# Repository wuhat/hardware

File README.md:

# WUHAT

A HAT for the Raspberry PI inspired by the
[franzboard](https://github.com/franzboard) and compatible in terms of switch
and LED connections.

## Features

* 1 DS18B20 temperature sensor
* 3 tactile switches
* 4 LEDs
* 1 ADC with 2 channels accessible via a header
* 6 GPIO pins on a header, surrounded by GND, 5V, and 3.3V
* 1 I2C pin header (GND SDA SCL 3V3)

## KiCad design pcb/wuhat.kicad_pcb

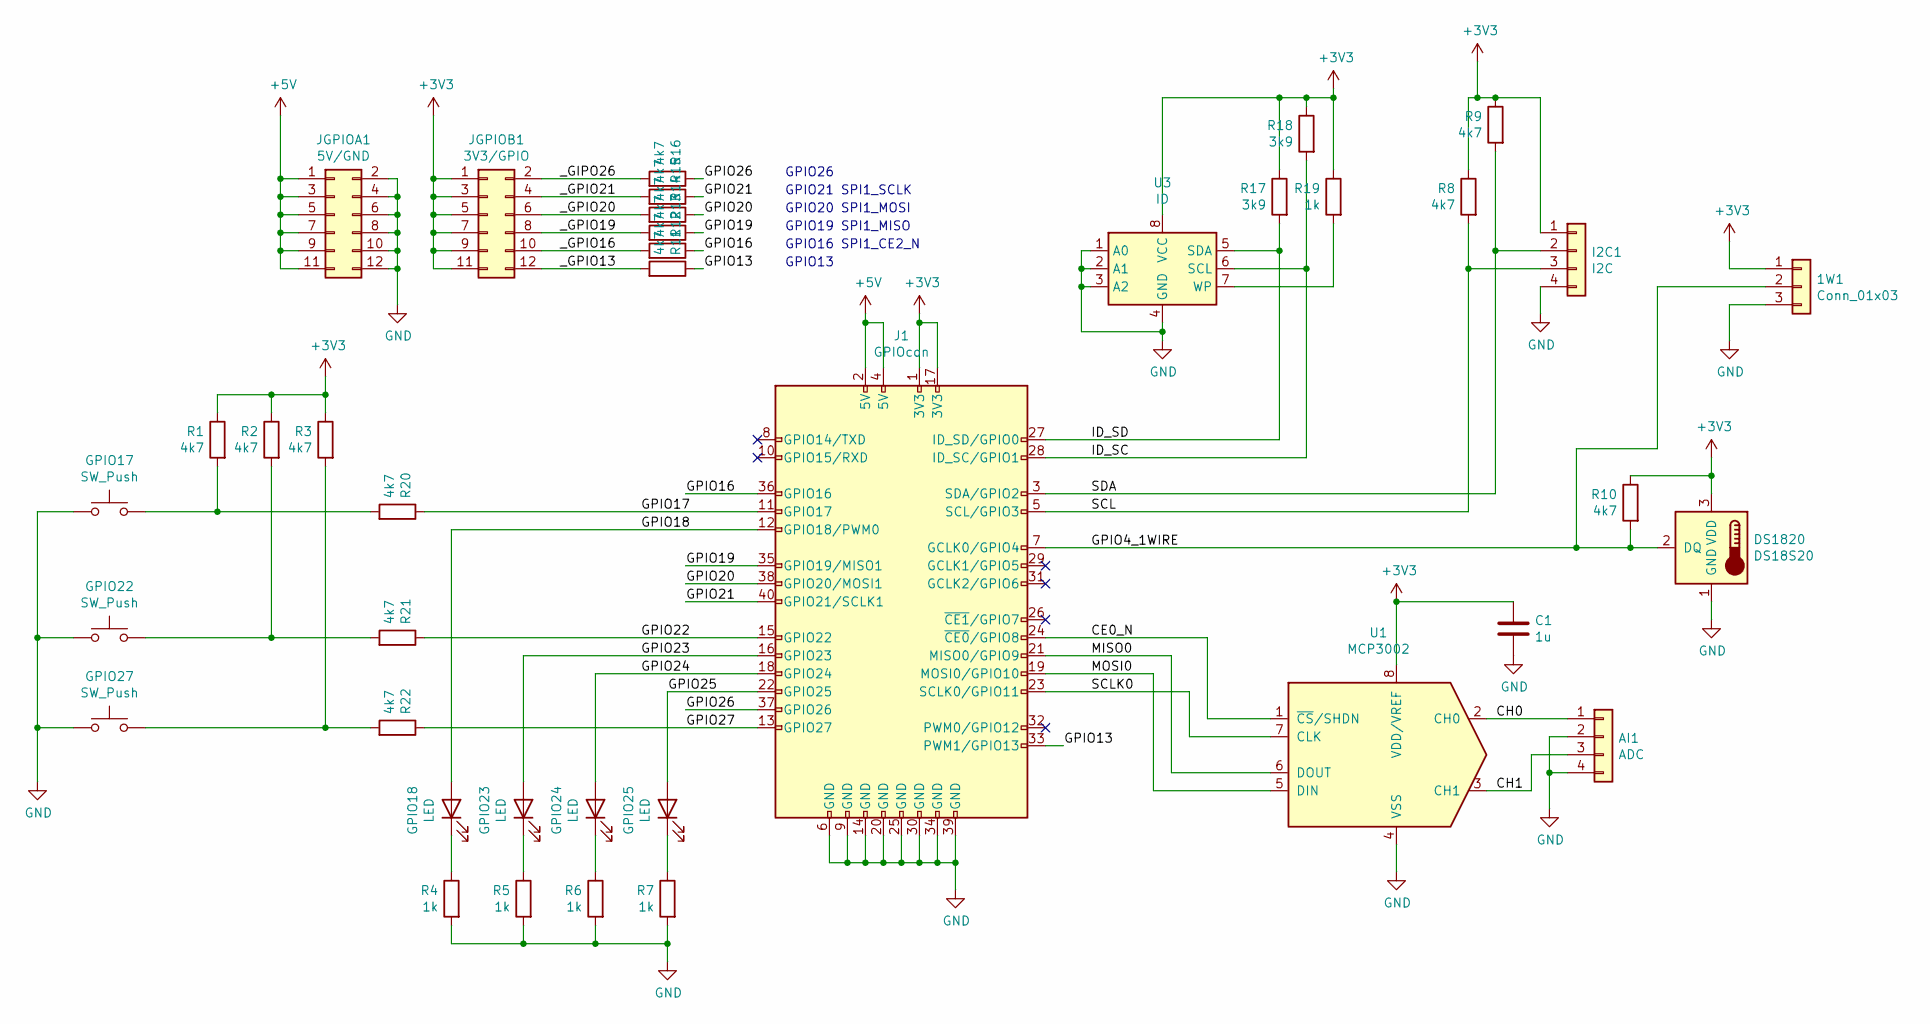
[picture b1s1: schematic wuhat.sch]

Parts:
1W1: Conn_01x03; PinHeader_1x03_P2.54mm_Vertical
AI1: ADC; PinHeader_1x04_P2.54mm_Vertical
C1: 1u; C_0603_1608Metric_Pad1.05x0.95mm_HandSolder
DS1820: DS18S20; TO-92_Inline_Wide
GPIO17, GPIO22, GPIO27: SW_Push; SW_PUSH_6mm
GPIO18, GPIO23, GPIO24, GPIO25: LED; LED_0603_1608Metric_Pad1.05x0.95mm_HandSolder
I2C1: I2C; PinHeader_1x04_P2.54mm_Vertical
J1: GPIOcon; PinHeader_2x20_P2.54mm_Vertical
JGPIOA1: 5V/GND; PinHeader_2x06_P2.54mm_Vertical
JGPIOB1: 3V3/GPIO; PinHeader_2x06_P2.54mm_Vertical
R1, R2, R3, R8, R9, R10, R11, R12, R13, R14, R15, R16, R20, R21, R22: 4k7; R_0603_1608Metric_Pad1.05x0.95mm_HandSolder
R4, R5, R6, R7, R19: 1k; R_0603_1608Metric_Pad1.05x0.95mm_HandSolder
R17, R18: 3k9; R_0603_1608Metric_Pad1.05x0.95mm_HandSolder
U1: MCP3002; SOIC-8_3.9x4.9mm_P1.27mm
U3: ID; SOIC-8_3.9x4.9mm_P1.27mm

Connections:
+3V3: 1W1.1, C1.1, DS1820.3 (VDD), I2C1.1, J1.1 (3V3), J1.17 (3V3), JGPIOB1.1, JGPIOB1.3, JGPIOB1.5, JGPIOB1.7, JGPIOB1.9, JGPIOB1.11, R1.1, R2.1, R3.1, R8.1, R9.1, R10.1, R17.1, R18.1, R19.1, U1.8 (VDD/VREF), U3.8 (VCC)
+5V: J1.2 (5V), J1.4 (5V), JGPIOA1.1, JGPIOA1.3, JGPIOA1.5, JGPIOA1.7, JGPIOA1.9, JGPIOA1.11
/CE0_N: J1.24 (~CE0~/GPIO8), U1.1 (~CS~/SHDN)
/CH0: AI1.1, U1.2 (CH0)
/CH1: AI1.3, U1.3 (CH1)
/GPIO4_1WIRE: 1W1.2, DS1820.2 (DQ), J1.7 (GCLK0/GPIO4), R10.2
/GPIO13: J1.33 (PWM1/GPIO13), R11.1
/GPIO16: J1.36 (GPIO16), R12.1
/GPIO17: J1.11 (GPIO17), R20.1
/GPIO18: GPIO18.2 (A), J1.12 (GPIO18/PWM0)
/GPIO19: J1.35 (GPIO19/MISO1), R13.1
/GPIO20: J1.38 (GPIO20/MOSI1), R14.1
/GPIO21: J1.40 (GPIO21/SCLK1), R15.1
/GPIO22: J1.15 (GPIO22), R21.1
/GPIO23: GPIO23.2 (A), J1.16 (GPIO23)
/GPIO24: GPIO24.2 (A), J1.18 (GPIO24)
/GPIO25: GPIO25.2 (A), J1.22 (GPIO25)
/GPIO26: J1.37 (GPIO26), R16.1
/GPIO27: J1.13 (GPIO27), R22.1
/ID_SC: J1.28 (ID_SC/GPIO1), R18.2, U3.6 (SCL)
/ID_SD: J1.27 (ID_SD/GPIO0), R17.2, U3.5 (SDA)
/MISO0: J1.21 (MISO0/GPIO9), U1.6 (DOUT)
/MOSI0: J1.19 (MOSI0/GPIO10), U1.5 (DIN)
/SCL: I2C1.3, J1.5 (SCL/GPIO3), R8.2
/SCLK0: J1.23 (SCLK0/GPIO11), U1.7 (CLK)
/SDA: I2C1.2, J1.3 (SDA/GPIO2), R9.2
/_GIPO26: JGPIOB1.2, R16.2
/_GPIO13: JGPIOB1.12, R11.2
/_GPIO16: JGPIOB1.10, R12.2
/_GPIO19: JGPIOB1.8, R13.2
/_GPIO20: JGPIOB1.6, R14.2
/_GPIO21: JGPIOB1.4, R15.2
GND: 1W1.3, AI1.2, AI1.4, C1.2, DS1820.1 (GND), GPIO17.1, GPIO22.1, GPIO27.1, I2C1.4, J1.6 (GND), J1.9 (GND), J1.14 (GND), J1.20 (GND), J1.25 (GND), J1.30 (GND), J1.34 (GND), J1.39 (GND), JGPIOA1.2, JGPIOA1.4, JGPIOA1.6, JGPIOA1.8, JGPIOA1.10, JGPIOA1.12, R4.2, R5.2, R6.2, R7.2, U1.4 (VSS), U3.1 (A0), U3.2 (A1), U3.3 (A2), U3.4 (GND)
unnamed: GPIO17.2, R1.2, R20.2
unnamed: GPIO18.1 (K), R4.1
unnamed: GPIO22.2, R2.2, R21.2
unnamed: GPIO23.1 (K), R5.1
unnamed: GPIO24.1 (K), R6.1
unnamed: GPIO25.1 (K), R7.1
unnamed: GPIO27.2, R3.2, R22.2
unnamed: R19.2, U3.7 (WP)

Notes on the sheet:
GPIO21 SPI1_SCLK
GPIO20 SPI1_MOSI
GPIO26
GPIO16 SPI1_CE2_N
GPIO19 SPI1_MISO
GPIO13

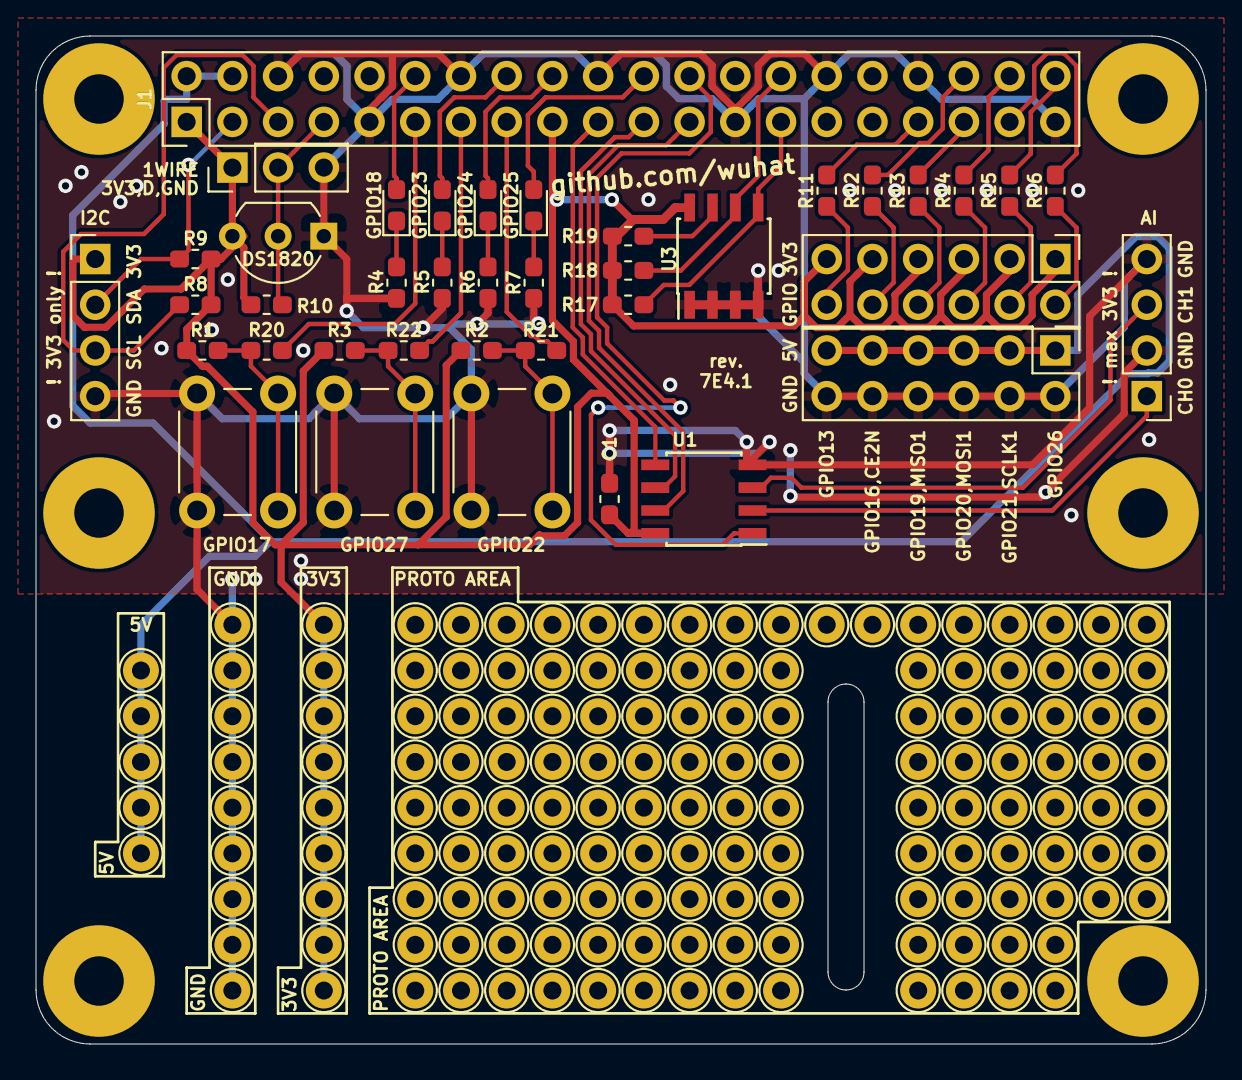
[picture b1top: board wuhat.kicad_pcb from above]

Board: 2 copper layers, 65.0 x 56.0 mm, 42 parts (1 on the bottom side), 41 nets.

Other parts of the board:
LOGO: qrcode
e: mounting_hole
e#2: mounting_hole

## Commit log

2018-12-04 first prototype run
2018-12-04 added schematic pdf
2018-12-07 added spacers
2019-11-18 added revision string to pcb
    bumped the revision to 7E4.0 (hex for 2020.0).
2019-12-05 BOM added
2019-12-05 added order information
2019-12-05 finished part numbers
2019-12-09 moved mounting holes and board outline
2019-12-09 expanded board to full size hat
2019-12-09 updated pdfs
2019-12-09 BOM updated and converted to xlsx
2020-01-13 fixed eeprom in bom
2020-02-03 notch added
2020-07-09 modified DS1820 footprint
